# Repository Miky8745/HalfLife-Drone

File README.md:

# HalfLife Drone
This is the project for week one and two of **Half Life**

It's an extension for an ESP32 S3 that allows it to safely control 4 coreless DC motors and get data from an IMU and Barometer units. Meaning it's prepared to be used in a quadcopter. And a frame for the drone itself.

Here's a nice render of the PCB.

And here's a nice render of the frame.

## BOM for week 1

### Assembled by JLCPCB (2 boards)

| Designator | Value | Footprint | Qty / board | Part # | Qty ordered* | Price | Source | Funded by |
| - | - | - | - | - | - | - | - | - |
| C1-C3, C8, C13 | 22u | 0805 | 5 | [C45783](https://www.lcsc.com/product-detail/C45783.html) | 10 | $2.21 | JLCPCB Assembly | Grant |
| C4, C5, C7, C9-C11, C14 | 100n | 0603 | 7 | [C14663](https://www.lcsc.com/product-detail/C14663.html) | 14 | $0.20 | JLCPCB Assembly | Grant |
| D1-D4 | SS34 | SMA | 4 | [C8678](https://www.lcsc.com/product-detail/C8678.html) | 8 | $0.28 | JLCPCB Assembly | Grant |
| D5 | SMBJ5.0A | SMB | 1 | [C19077558](https://www.lcsc.com/product-detail/C19077558.html) | 5 | $0.24 | JLCPCB Assembly | Grant |
| D6 | B5819W | SOD-123 | 1 | [C8598](https://www.lcsc.com/product-detail/C8598.html) | 2 | $0.06 | JLCPCB Assembly | Grant |
| D7, D8 | Red LED | 0603 | 2 | [C2286](https://www.lcsc.com/product-detail/C2286.html) | 4 | $0.03 | JLCPCB Assembly | Grant |
| L1 | 0.47 µH | 2016 | 1 | [C668312](https://www.lcsc.com/product-detail/C668312.html) | 5 | $0.89 | JLCPCB Assembly | Grant |
| Q1-Q4 | AO3400A | SOT-23 | 4 | [C20917](https://www.lcsc.com/product-detail/C20917.html) | 8 | $0.71 | JLCPCB Assembly | Grant |
| R1, R2, R10, R11 | 100 | 0603 | 4 | [C22775](https://www.lcsc.com/product-detail/C22775.html) | 8 | $0.02 | JLCPCB Assembly | Grant |
| R3, R4, R7, R13-R16 | 10k | 0603 | 7 | [C25804](https://www.lcsc.com/product-detail/C25804.html) | 14 | $0.03 | JLCPCB Assembly | Grant |
| R5, R8, R9 | 100k | 0603 | 3 | [C25803](https://www.lcsc.com/product-detail/C25803.html) | 6 | $0.02 | JLCPCB Assembly | Grant |
| R6 | 56k | 0603 | 1 | [C23206](https://www.lcsc.com/product-detail/C23206.html) | 2 | $0.01 | JLCPCB Assembly | Grant |
| R17, R18 | 1k | 0603 | 2 | [C21190](https://www.lcsc.com/product-detail/C21190.html) | 4 | $0.01 | JLCPCB Assembly | Grant |
| U2 | TPS63802DLAR | VSON-10 | 1 | [C2845237](https://www.lcsc.com/product-detail/C2845237.html) | 2 | $1.81 | JLCPCB Assembly | Grant |
| U3 | MS5611-01BA | LGA-8 | 1 | [C15639](https://www.lcsc.com/product-detail/C15639.html) | 2 | $13.43 | JLCPCB Assembly | Grant |
| | | | | | | **$19.94** | | |

- `*` Some parts have a minimum order quantity amount (like the L1), that's why there's more ordered then I need

### Hand-soldered (bought by me)

| Designator | Value | Footprint | Qty / board | URL | Price | Source | Funded by |
| - | - | - | - | - | - | - | - |
| C6 | 220u 16V electrolytic | Radial D6.3 mm, 2.5 mm pitch | 1 | [Radiokus](https://www.radiokus.cz/220uF-16V-elektrolyticky-radialni-kondenzator-d2327.htm) | 3 Kč | Self-sourced | Me |
| SW1 | S103mini SPDT slide switch | 3 pin, 2.54 mm | 1 | [Radiokus](https://www.radiokus.cz/Posuvny-prepinac-jednoduchy-do-DPS-d4843.htm) | 7 Kč | Self-sourced | Me |
| J5, J7, J10 | Female header 1x40, cut to 1x22 + 1x22 + 1x08 | 2.54 mm | 2 strips | [Radiokus](https://www.radiokus.cz/zasuvka-1-x-40-pinu-do-dps-prima-rastr-2-54mm) | 50 Kč | Self-sourced | Me |
| J8, J9 | Male header 1x11, cut to 1x04 + 1x06 | 2.54 mm | 1 strip | [Radiokus](https://www.radiokus.cz/Vidlice-1-x-11-pinu-do-DPS-prima-rastr-2-54mm-d3864.htm) | 8 Kč | Self-sourced | Me |

### Funding request (JLCPCB order)

| Item | Price |
| - | - |
| PCB (5 pcs, 4 layer) | $8.00 |
| Assembly setup fee | $8.24 |
| Components | $19.94 |
| Extended components fee | $9.27 |
| SMT assembly | $0.38 |
| Confirm parts placement | $0.45 |
| Other order options | $2.41 |
| Shipping | $9.32 |
| Customs duties & taxes | $17.07 |
| Discount coupon | -$10.00 |
| **Total** | **$65.08** |

Here's the BOM as a csv: [BOM.csv](/BOM.csv)

## Structure
 - `esp_extension/` - KiCad files (including production files under `esp_extension/production`)
 - `motor_test/` - A quick test with an AI generated script for driving the coreless motor
- `frame/` - Files for week 2

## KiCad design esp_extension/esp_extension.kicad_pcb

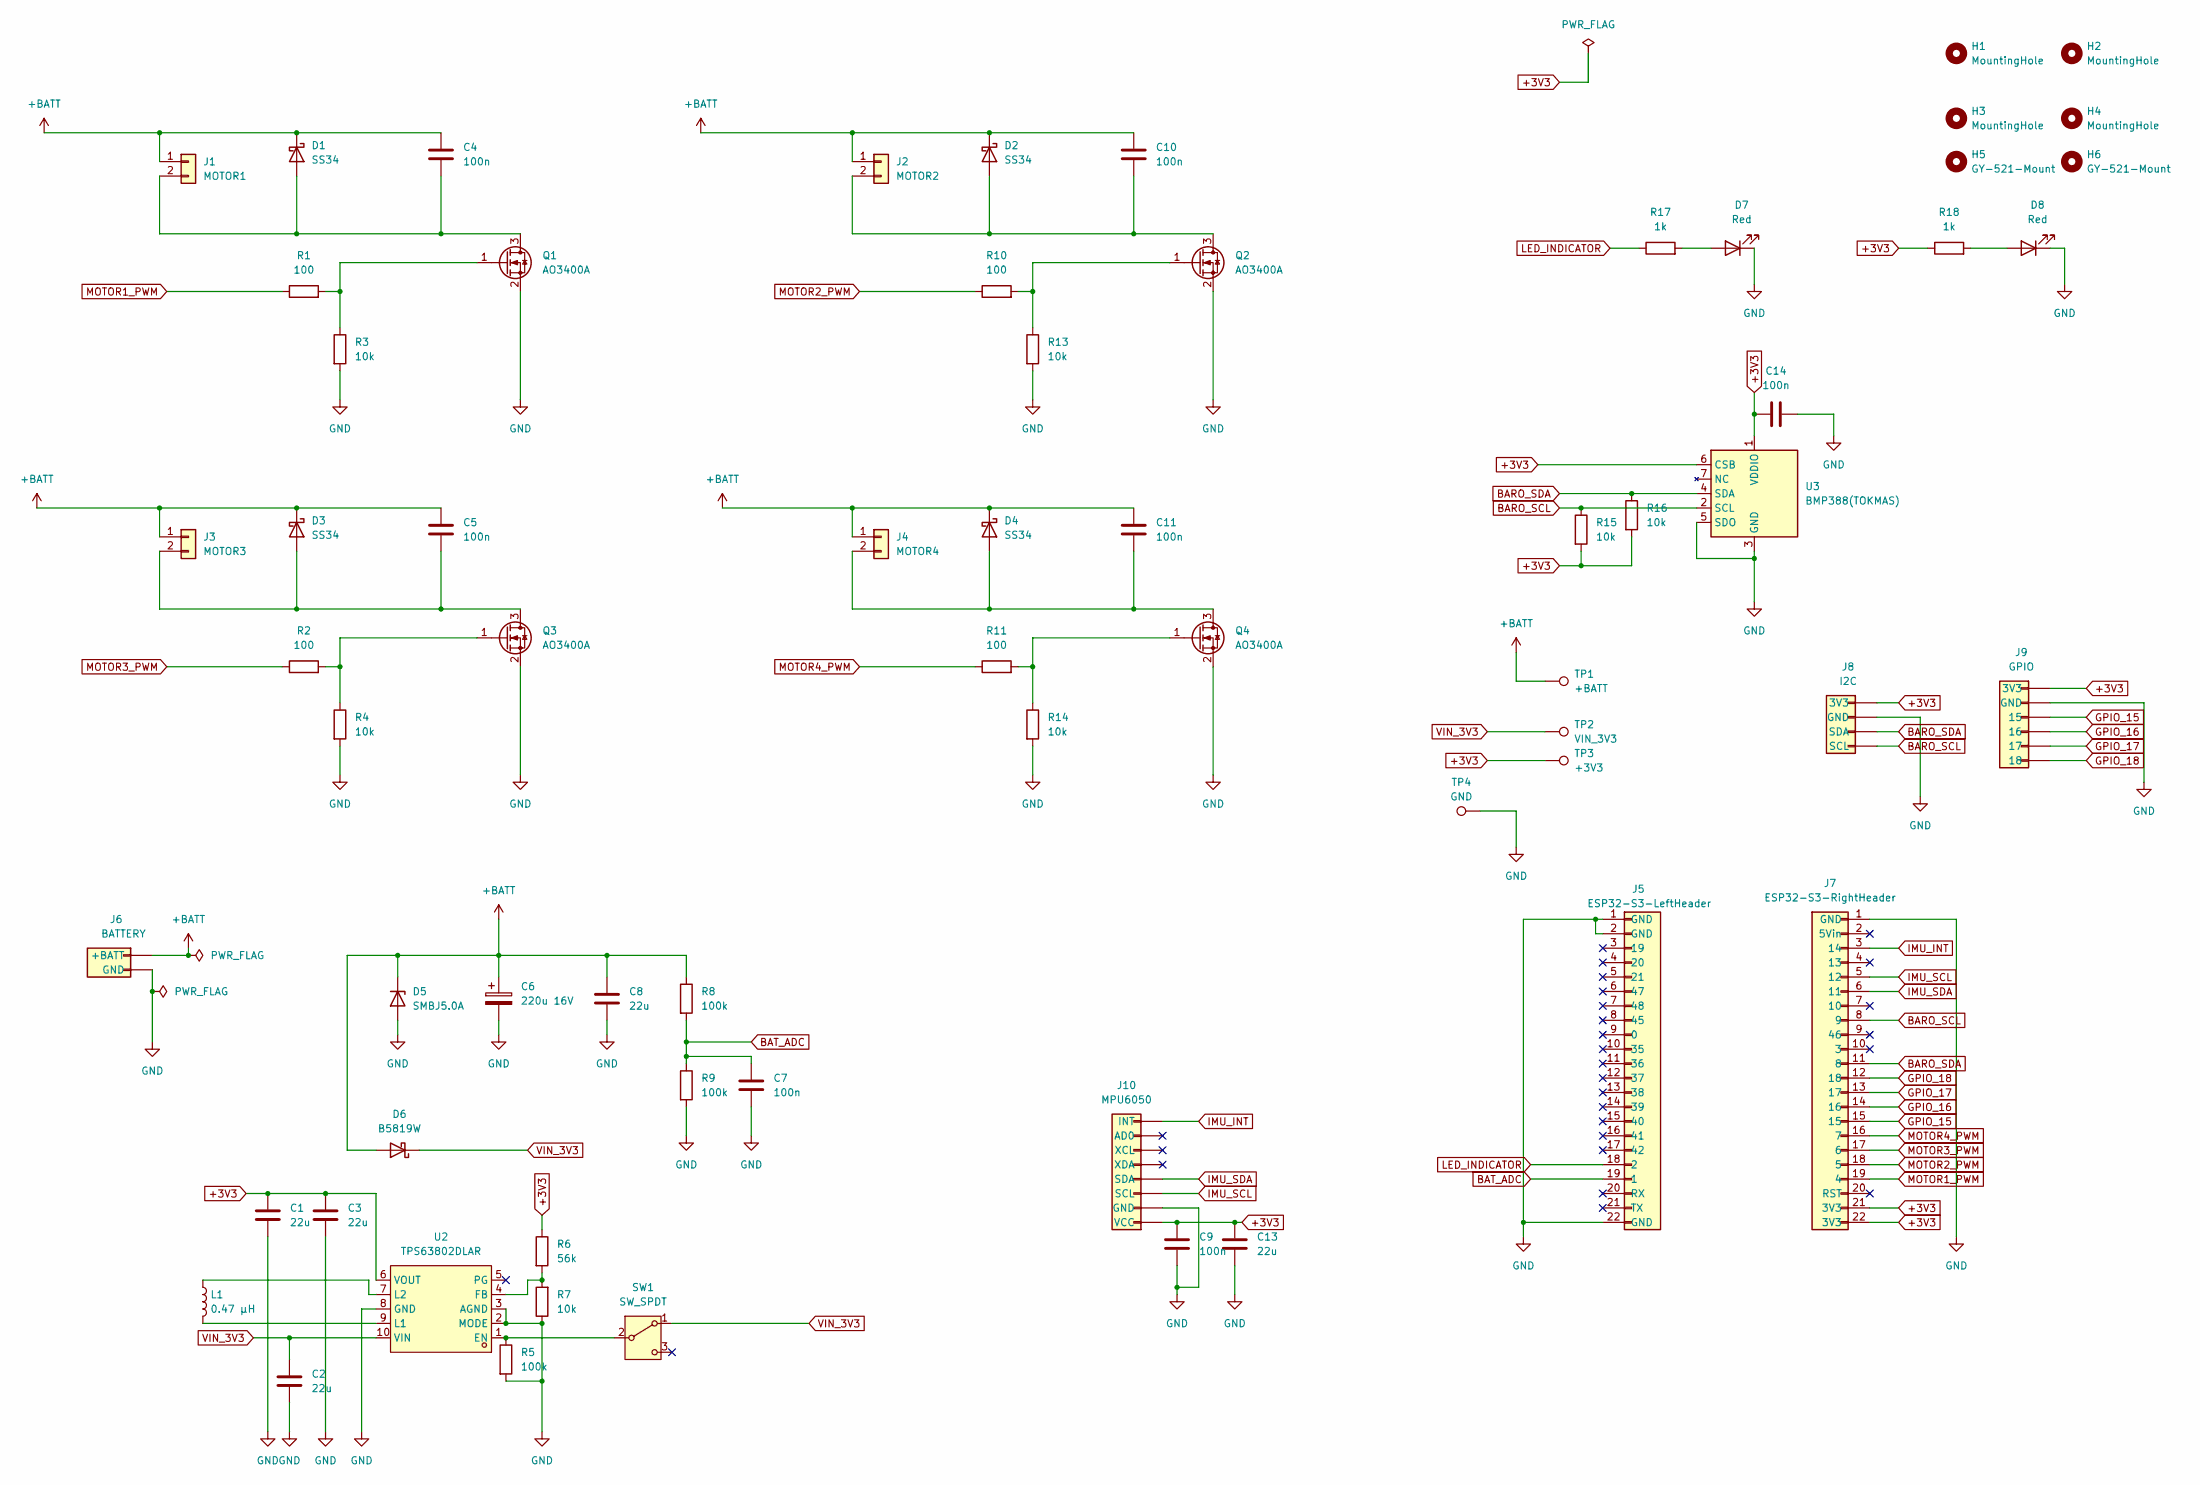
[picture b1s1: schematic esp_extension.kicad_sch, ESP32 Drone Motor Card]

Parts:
C1, C2, C3, C8, C13: 22u; C_0805_2012Metric; MPN CL21A226MAQNNNE; LCSC Part C45783
C4, C5, C7, C9, C10, C11, C14: 100n; C_0603_1608Metric; MPN CC0603KRX7R9BB104; LCSC Part C14663
C6: 220u 16V; CP_Radial_D6.3mm_P2.50mm; MPN TFR_220_16_85
D1, D2, D3, D4: SS34; D_SMA; MPN SS34; LCSC Part C8678
D5: SMBJ5.0A; D_SMB; MPN SMBJ5.0A; LCSC Part C19077558
D6: B5819W; D_SOD-123; MPN B5819W SL; LCSC Part C8598
D7, D8: Red; LED_0603_1608Metric; MPN KT-0603R; LCSC Part C2286
H1, H2, H3, H4: MountingHole; MountingHole_2.2mm_M2
H5, H6: GY-521-Mount; MountingHole_3.2mm_M3
J1: MOTOR1; SolderWire-0.25sqmm_1x02_P4.2mm_D0.65mm_OD1.7mm
J2: MOTOR2; SolderWire-0.25sqmm_1x02_P4.2mm_D0.65mm_OD1.7mm
J3: MOTOR3; SolderWire-0.25sqmm_1x02_P4.2mm_D0.65mm_OD1.7mm
J4: MOTOR4; SolderWire-0.25sqmm_1x02_P4.2mm_D0.65mm_OD1.7mm
J5: ESP32-S3-LeftHeader; PinSocket_1x22_P2.54mm_Vertical
J6: BATTERY; SolderWire-0.5sqmm_1x02_P4.8mm_D0.9mm_OD2.3mm
J7: ESP32-S3-RightHeader; PinSocket_1x22_P2.54mm_Vertical
J8: I2C; PinHeader_1x04_P2.54mm_Vertical
J9: GPIO; PinHeader_1x06_P2.54mm_Vertical
J10: MPU6050; PinSocket_1x08_P2.54mm_Vertical
L1: 0.47 µH; IND-SMD_L2.0-W1.6-1; MPN DFE201612E-R47M=P2; LCSC Part C668312
Q1, Q2, Q3, Q4: AO3400A; SOT-23; MPN AO3400A; LCSC Part C20917
R1, R2, R10, R11: 100; R_0603_1608Metric; MPN 0603WAF1000T5E; LCSC Part C22775
R3, R4, R7, R13, R14, R15, R16: 10k; R_0603_1608Metric; MPN 0603WAF1002T5E; LCSC Part C25804
R5, R8, R9: 100k; R_0603_1608Metric; MPN 0603WAF1003T5E; LCSC Part C25803
R6: 56k; R_0603_1608Metric; MPN 0603WAF5602T5E; LCSC Part C23206
R17, R18: 1k; R_0603_1608Metric; MPN 0603WAF1001T5E; LCSC Part C21190
SW1: SW_SPDT; PinHeader_1x03_P2.54mm_Vertical; MPN S103mini
TP1: +BATT; TestPoint_Pad_D1.5mm
TP2: VIN_3V3; TestPoint_Pad_D1.5mm
TP3: +3V3; TestPoint_Pad_D1.5mm
TP4: GND; TestPoint_Pad_D1.5mm
U2: TPS63802DLAR; VSON-10_L3.0-W2.0-P0.50-TL; MPN TPS63802DLAR; LCSC Part C2845237
U3: BMP388(TOKMAS); BMP388_LGA10_2x2mm_P0.5mm; MPN BMP388(TOKMAS); LCSC Part C54582187

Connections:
+3V3: C1.1, C3.1, C9.2, C13.1, C14.1, J7.21 (3V3), J7.22 (3V3), J8.1 (3V3), J9.1 (3V3), J10.1 (VCC), R6.1, R15.2, R16.2, R18.1, TP3.1 (1_1), U2.6 (VOUT), U3.1 (VDDIO), U3.6 (CSB), U3.10 (VDD)
+BATT: C4.1, C5.1, C6.1, C8.1, C10.1, C11.1, D1.1 (K), D2.1 (K), D3.1 (K), D4.1 (K), D5.1 (K), D6.2 (A), J1.1, J2.1, J3.1, J4.1, J6.1 (+BATT), R8.1, TP1.1 (1_1)
BARO_SCL: J7.8 (9), J8.4 (SCL), R15.1, U3.2 (SCL)
BARO_SDA: J7.11 (8), J8.3 (SDA), R16.1, U3.4 (SDA)
BAT_ADC: C7.1, J5.19 (1), R8.2, R9.1
GND: C1.2, C2.2, C3.2, C6.2, C7.2, C8.2, C9.1, C13.2, C14.2, D5.2 (A), D7.1 (K), D8.1 (K), J5.1 (GND), J5.2 (GND), J5.22 (GND), J6.2 (GND), J7.1 (GND), J8.2 (GND), J9.2 (GND), J10.2 (GND), Q1.2 (S), Q2.2 (S), Q3.2 (S), Q4.2 (S), R3.2, R4.2, R5.2, R7.1, R9.2, R13.2, R14.2, TP4.1 (1_1), U2.2 (MODE), U2.3 (AGND), U2.8 (GND), U3.3 (GND), U3.5 (SDO), U3.8 (GND), U3.9 (GND)
GPIO_15: J7.15, J9.3 (15)
GPIO_16: J7.14 (16), J9.4 (16)
GPIO_17: J7.13 (17), J9.5 (17)
GPIO_18: J7.12 (18), J9.6 (18)
IMU_INT: J7.3 (14), J10.8 (INT)
IMU_SCL: J7.5 (12), J10.3 (SCL)
IMU_SDA: J7.6 (11), J10.4 (SDA)
LED_INDICATOR: J5.18 (2), R17.1
MOTOR1_PWM: J7.19 (4), R1.1
MOTOR2_PWM: J7.18 (5), R10.1
MOTOR3_PWM: J7.17 (6), R2.1
MOTOR4_PWM: J7.16 (7), R11.1
unnamed: C4.2, D1.2 (A), J1.2, Q1.3 (D)
unnamed: C10.2, D2.2 (A), J2.2, Q2.3 (D)
unnamed: C5.2, D3.2 (A), J3.2, Q3.3 (D)
unnamed: C11.2, D4.2 (A), J4.2, Q4.3 (D)
unnamed: D7.2 (A), R17.2
unnamed: D8.2 (A), R18.2
unnamed: Q1.1 (G), R1.2, R3.1
unnamed: Q2.1 (G), R10.2, R13.1
unnamed: Q3.1 (G), R2.2, R4.1
unnamed: Q4.1 (G), R11.2, R14.1
unnamed: R5.1, SW1.2 (B), U2.1 (EN)
unnamed: R6.2, R7.2, U2.4 (FB)
unnamed: L1.2, U2.9 (L1)
unnamed: L1.1, U2.7 (L2)
VIN_3V3: C2.1, D6.1 (K), SW1.1 (A), TP2.1 (1_1), U2.10 (VIN)

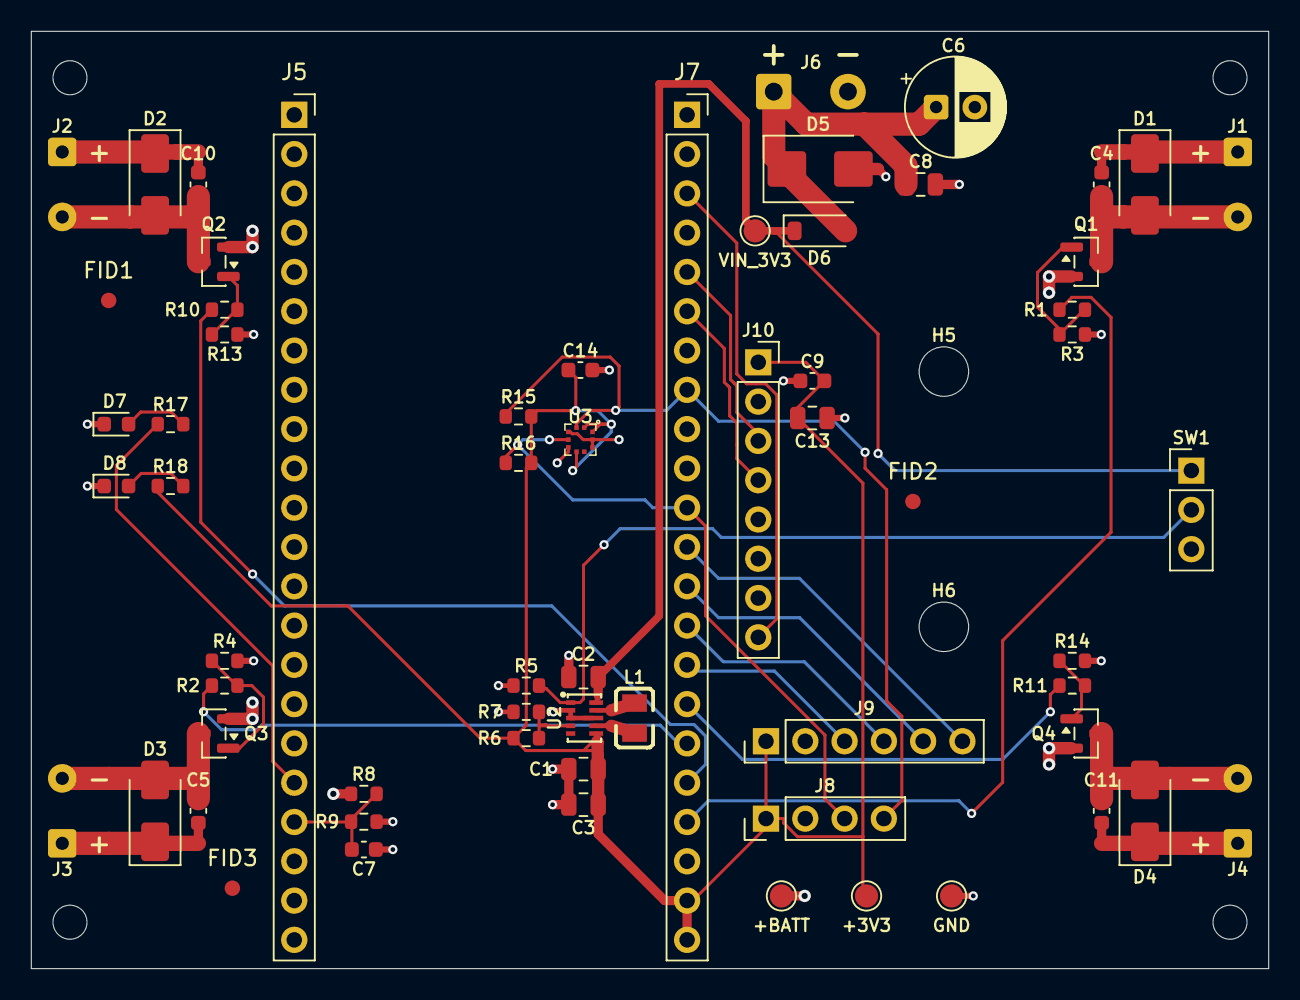
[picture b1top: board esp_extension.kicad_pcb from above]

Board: 4 copper layers, 80.0 x 60.6 mm, 69 parts (0 on the bottom side), 33 nets.

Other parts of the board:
FID1, FID2, FID3: Fiducial_1mm_Mask2mm

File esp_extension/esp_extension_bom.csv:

"Reference","Value","Footprint","Qty","LCSC Part","MPN","Manufacturer"
"C1-C3,C8,C13","22u","Capacitor_SMD:C_0805_2012Metric","5","C45783","CL21A226MAQNNNE","Samsung"
"C4,C5,C7,C9-C11,C14","100n","Capacitor_SMD:C_0603_1608Metric","7","C14663","CC0603KRX7R9BB104","Yageo"
"D1-D4","SS34","Diode_SMD:D_SMA","4","C8678","SS34","MDD"
"D5","SMBJ5.0A","Diode_SMD:D_SMB","1","C19077558","SMBJ5.0A","Hongjiacheng"
"D6","B5819W","Diode_SMD:D_SOD-123","1","C8598","B5819W SL","Changjiang"
"D7,D8","Red","LED_SMD:LED_0603_1608Metric","2","C2286","KT-0603R","Kento"
"L1","0.47 µH","drone:IND-SMD_L2.0-W1.6-1","1","C668312","DFE201612E-R47M=P2","Murata"
"Q1-Q4","AO3400A","Package_TO_SOT_SMD:SOT-23","4","C20917","AO3400A","AOS"
"R1,R2,R10,R11","100","Resistor_SMD:R_0603_1608Metric","4","C22775","0603WAF1000T5E","Uni-Royal"
"R3,R4,R7,R13-R16","10k","Resistor_SMD:R_0603_1608Metric","7","C25804","0603WAF1002T5E","Uni-Royal"
"R5,R8,R9","100k","Resistor_SMD:R_0603_1608Metric","3","C25803","0603WAF1003T5E","Uni-Royal"
"R6","56k","Resistor_SMD:R_0603_1608Metric","1","C23206","0603WAF5602T5E","Uni-Royal"
"R17,R18","1k","Resistor_SMD:R_0603_1608Metric","2","C21190","0603WAF1001T5E","Uni-Royal"
"U2","TPS63802DLAR","drone:VSON-10_L3.0-W2.0-P0.50-TL","1","C2845237","TPS63802DLAR","Texas Instruments"
"U3","MS5611-01BA","Package_LGA:LGA-8_3x5mm_P1.25mm","1","C15639","MS561101BA03-50","TE Connectivity"
